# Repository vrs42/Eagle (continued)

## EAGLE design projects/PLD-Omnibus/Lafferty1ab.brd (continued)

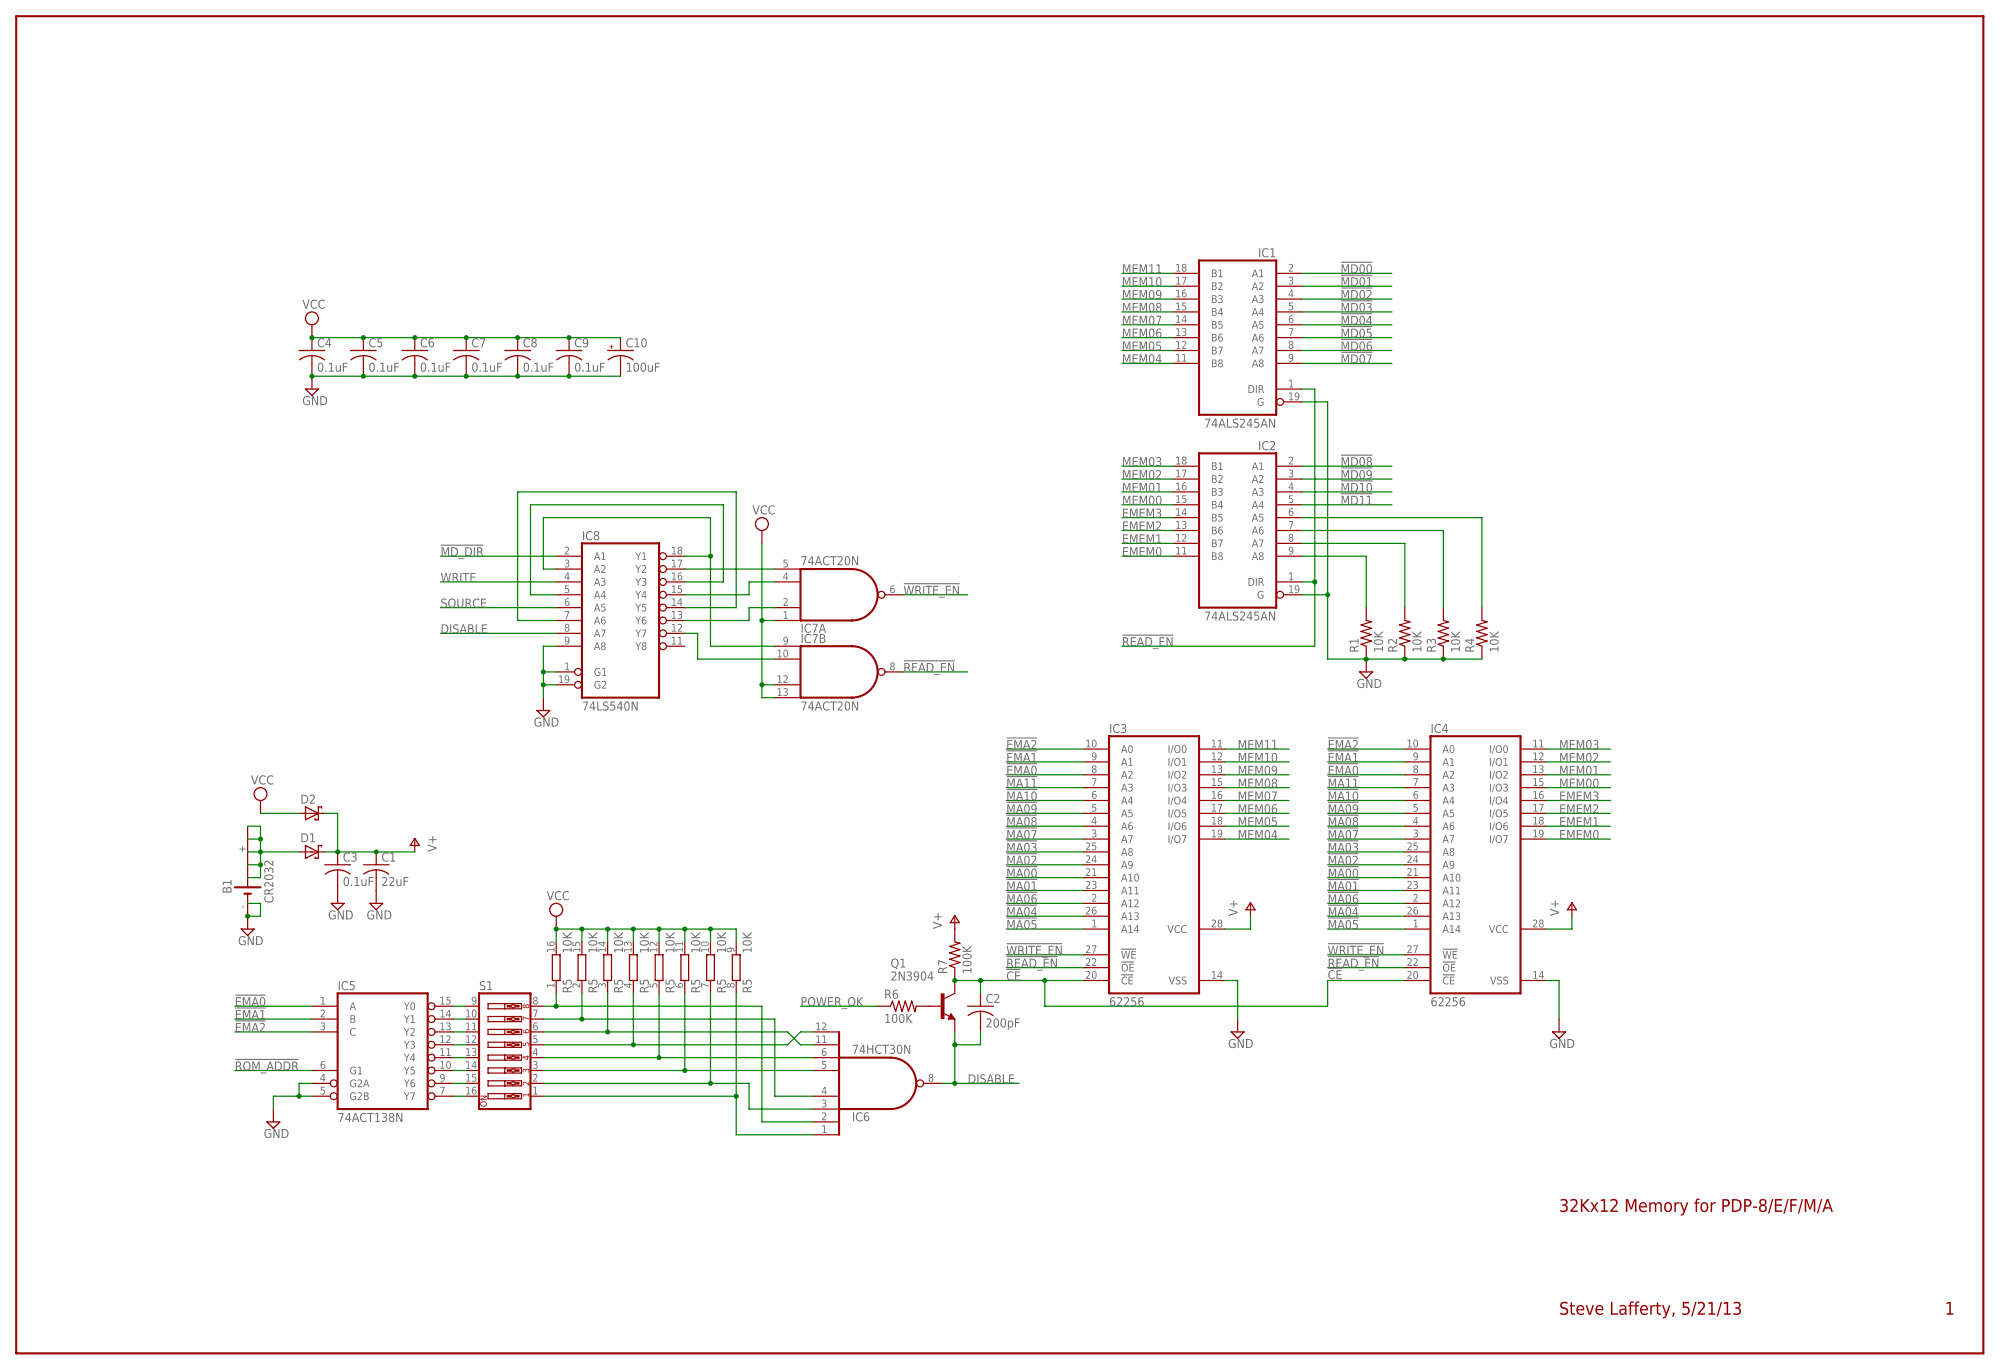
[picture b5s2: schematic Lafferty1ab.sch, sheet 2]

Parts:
B1: CR2032; B2430UNI
C1: 22uF; C050-025X075
C2: 200pF; C050-025X075
C3, C4, C5, C6, C7, C8, C9: 0.1uF; C050-025X075
C10: 100uF; E12-8
D1, D2: BAT19; DO35-10
IC1, IC2: 74ALS245AN; DIL20
IC3, IC4: 62256; DIL28-6
IC5: 74ACT138N; DIL16
IC6: 74HCT30N; DIL14
IC7: 74ACT20N; DIL14
IC8: 74LS540N; DIL20
Q1: 2N3904; TO92
R1, R2, R3, R4: 10K; 0207/10
R5: 10K; DIL16
R6, R7: 100K; 0207/10
S1: SW_DIP-8; EDG-08

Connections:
!CE: C2.1, IC3.20 (!CE), IC4.20 (!CE), Q1.1 (C), R7.1
!EMA0: IC3.8 (A2), IC4.8 (A2), IC5.1 (A); also elsewhere on the board
!EMA1: IC3.9 (A1), IC4.9 (A1), IC5.2 (B); also elsewhere on the board
!EMA2: IC3.10 (A0), IC4.10 (A0), IC5.3 (C); also elsewhere on the board
!MA00: IC3.21 (A10), IC4.21 (A10); also elsewhere on the board
!MA01: IC3.23 (A11), IC4.23 (A11); also elsewhere on the board
!MA02: IC3.24 (A9), IC4.24 (A9); also elsewhere on the board
!MA03: IC3.25 (A8), IC4.25 (A8); also elsewhere on the board
!MA04: IC3.26 (A13), IC4.26 (A13); also elsewhere on the board
!MA05: IC3.1 (A14), IC4.1 (A14); also elsewhere on the board
!MA06: IC3.2 (A12), IC4.2 (A12); also elsewhere on the board
!MA07: IC3.3 (A7), IC4.3 (A7); also elsewhere on the board
!MA08: IC3.4 (A6), IC4.4 (A6); also elsewhere on the board
!MA09: IC3.5 (A5), IC4.5 (A5); also elsewhere on the board
!MA10: IC3.6 (A4), IC4.6 (A4); also elsewhere on the board
!MA11: IC3.7 (A3), IC4.7 (A3); also elsewhere on the board
!MD00: IC1.2 (A1); also elsewhere on the board
!MD01: IC1.3 (A2); also elsewhere on the board
!MD02: IC1.4 (A3); also elsewhere on the board
!MD03: IC1.5 (A4); also elsewhere on the board
!MD04: IC1.6 (A5); also elsewhere on the board
!MD05: IC1.7 (A6); also elsewhere on the board
!MD06: IC1.8 (A7); also elsewhere on the board
!MD07: IC1.9 (A8); also elsewhere on the board
!MD08: IC2.2 (A1); also elsewhere on the board
!MD09: IC2.3 (A2); also elsewhere on the board
!MD10: IC2.4 (A3); also elsewhere on the board
!MD11: IC2.5 (A4); also elsewhere on the board
!MD_DIR: IC8.2 (A1); also elsewhere on the board
!READ_EN: IC1.1 (DIR), IC2.1 (DIR), IC3.22 (!OE), IC4.22 (!OE), IC7.8 (O)
!ROM_ADDR: IC5.6 (G1); also elsewhere on the board
!WRITE_EN: IC3.27 (!WE), IC4.27 (!WE), IC7.6 (O)
DISABLE: C2.2, IC6.8 (O), IC8.8 (A7), Q1.3 (E)
EMEM0: IC2.11 (B8), IC4.19 (I/O7)
EMEM1: IC2.12 (B7), IC4.18 (I/O6)
EMEM2: IC2.13 (B6), IC4.17 (I/O5)
EMEM3: IC2.14 (B5), IC4.16 (I/O4)
GND: B1.-, B1.-@1 (-), C1.2, C3.2, C4.2, C5.2, C6.2, C7.2, C8.2, C9.2, C10.-, IC1.10 (GND), IC1.19 (G), IC2.10 (GND), IC2.19 (G), IC3.14 (VSS), IC4.14 (VSS), IC5.4 (G2A), IC5.5 (G2B), IC5.8 (GND), IC6.7 (GND), IC7.7 (GND), IC8.1 (G1), IC8.9 (A8), IC8.10 (GND), IC8.19 (G2), R1.1, R2.1, R3.1, R4.1; also elsewhere on the board
MEM00: IC2.15 (B4), IC4.15 (I/O3)
MEM01: IC2.16 (B3), IC4.13 (I/O2)
MEM02: IC2.17 (B2), IC4.12 (I/O1)
MEM03: IC2.18 (B1), IC4.11 (I/O0)
MEM04: IC1.11 (B8), IC3.19 (I/O7)
MEM05: IC1.12 (B7), IC3.18 (I/O6)
MEM06: IC1.13 (B6), IC3.17 (I/O5)
MEM07: IC1.14 (B5), IC3.16 (I/O4)
MEM08: IC1.15 (B4), IC3.15 (I/O3)
MEM09: IC1.16 (B3), IC3.13 (I/O2)
MEM10: IC1.17 (B2), IC3.12 (I/O1)
MEM11: IC1.18 (B1), IC3.11 (I/O0)
unnamed: IC5.7 (Y7), S1.16
unnamed: IC5.9 (Y6), S1.15
unnamed: IC5.10 (Y5), S1.14
unnamed: IC5.11 (Y4), S1.13
unnamed: IC5.12 (Y3), S1.12
unnamed: IC5.13 (Y2), S1.11
unnamed: IC5.14 (Y1), S1.10
unnamed: IC5.15 (Y0), S1.9
unnamed: B1.+, B1.+@1 (+), B1.+@2 (+), B1.+@3 (+), B1.+@4 (+), D1.A
unnamed: IC6.12 (I7), R5.4 (1), S1.5
unnamed: IC6.11 (I6), R5.3 (1), S1.6
unnamed: IC6.6 (I5), R5.5 (1), S1.4
unnamed: IC6.5 (I4), R5.6 (1), S1.3
unnamed: IC6.3 (I2), R5.7 (1), S1.2
unnamed: IC6.1 (I0), R5.8 (1), S1.1
unnamed: IC6.2 (I1), R5.1, S1.8
unnamed: IC6.4 (I3), R5.2 (1), S1.7
unnamed: IC7.5 (I3), IC8.17 (Y2)
unnamed: IC2.6 (A5), R4.2
unnamed: Q1.2 (B), R6.2
unnamed: IC2.7 (A6), R3.2
unnamed: IC2.8 (A7), R2.2
unnamed: IC2.9 (A8), R1.2
unnamed: IC8.5 (A4), IC8.16 (Y3)
unnamed: IC7.9 (I0), IC8.3 (A2), IC8.18 (Y1)
unnamed: IC8.7 (A6), IC8.14 (Y5)
unnamed: IC7.2 (I1), IC8.13 (Y6)
unnamed: IC7.4 (I2), IC8.15 (Y4)
unnamed: IC7.10 (I1), IC8.12 (Y7)
POWER_OK: R6.1; also elsewhere on the board
SOURCE: IC8.6 (A5); also elsewhere on the board
V+: C1.1, C3.1, D1.C, D2.C, IC3.28 (VCC), IC4.28 (VCC), R7.2
VCC: C4.1, C5.1, C6.1, C7.1, C8.1, C9.1, C10.+, D2.A, IC1.20 (VCC), IC2.20 (VCC), IC5.16 (VCC), IC6.14 (VCC), IC7.1 (I0), IC7.12 (I2), IC7.13 (I3), IC7.14 (VCC), IC8.20 (VCC), R5.9 (2), R5.10 (2), R5.11 (2), R5.12 (2), R5.13 (2), R5.14 (2), R5.15 (2), R5.16 (2); also elsewhere on the board
WRITE: IC8.4 (A3); also elsewhere on the board

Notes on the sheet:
32Kx12 Memory for PDP-8/E/F/M/A
Steve Lafferty, 5/21/13

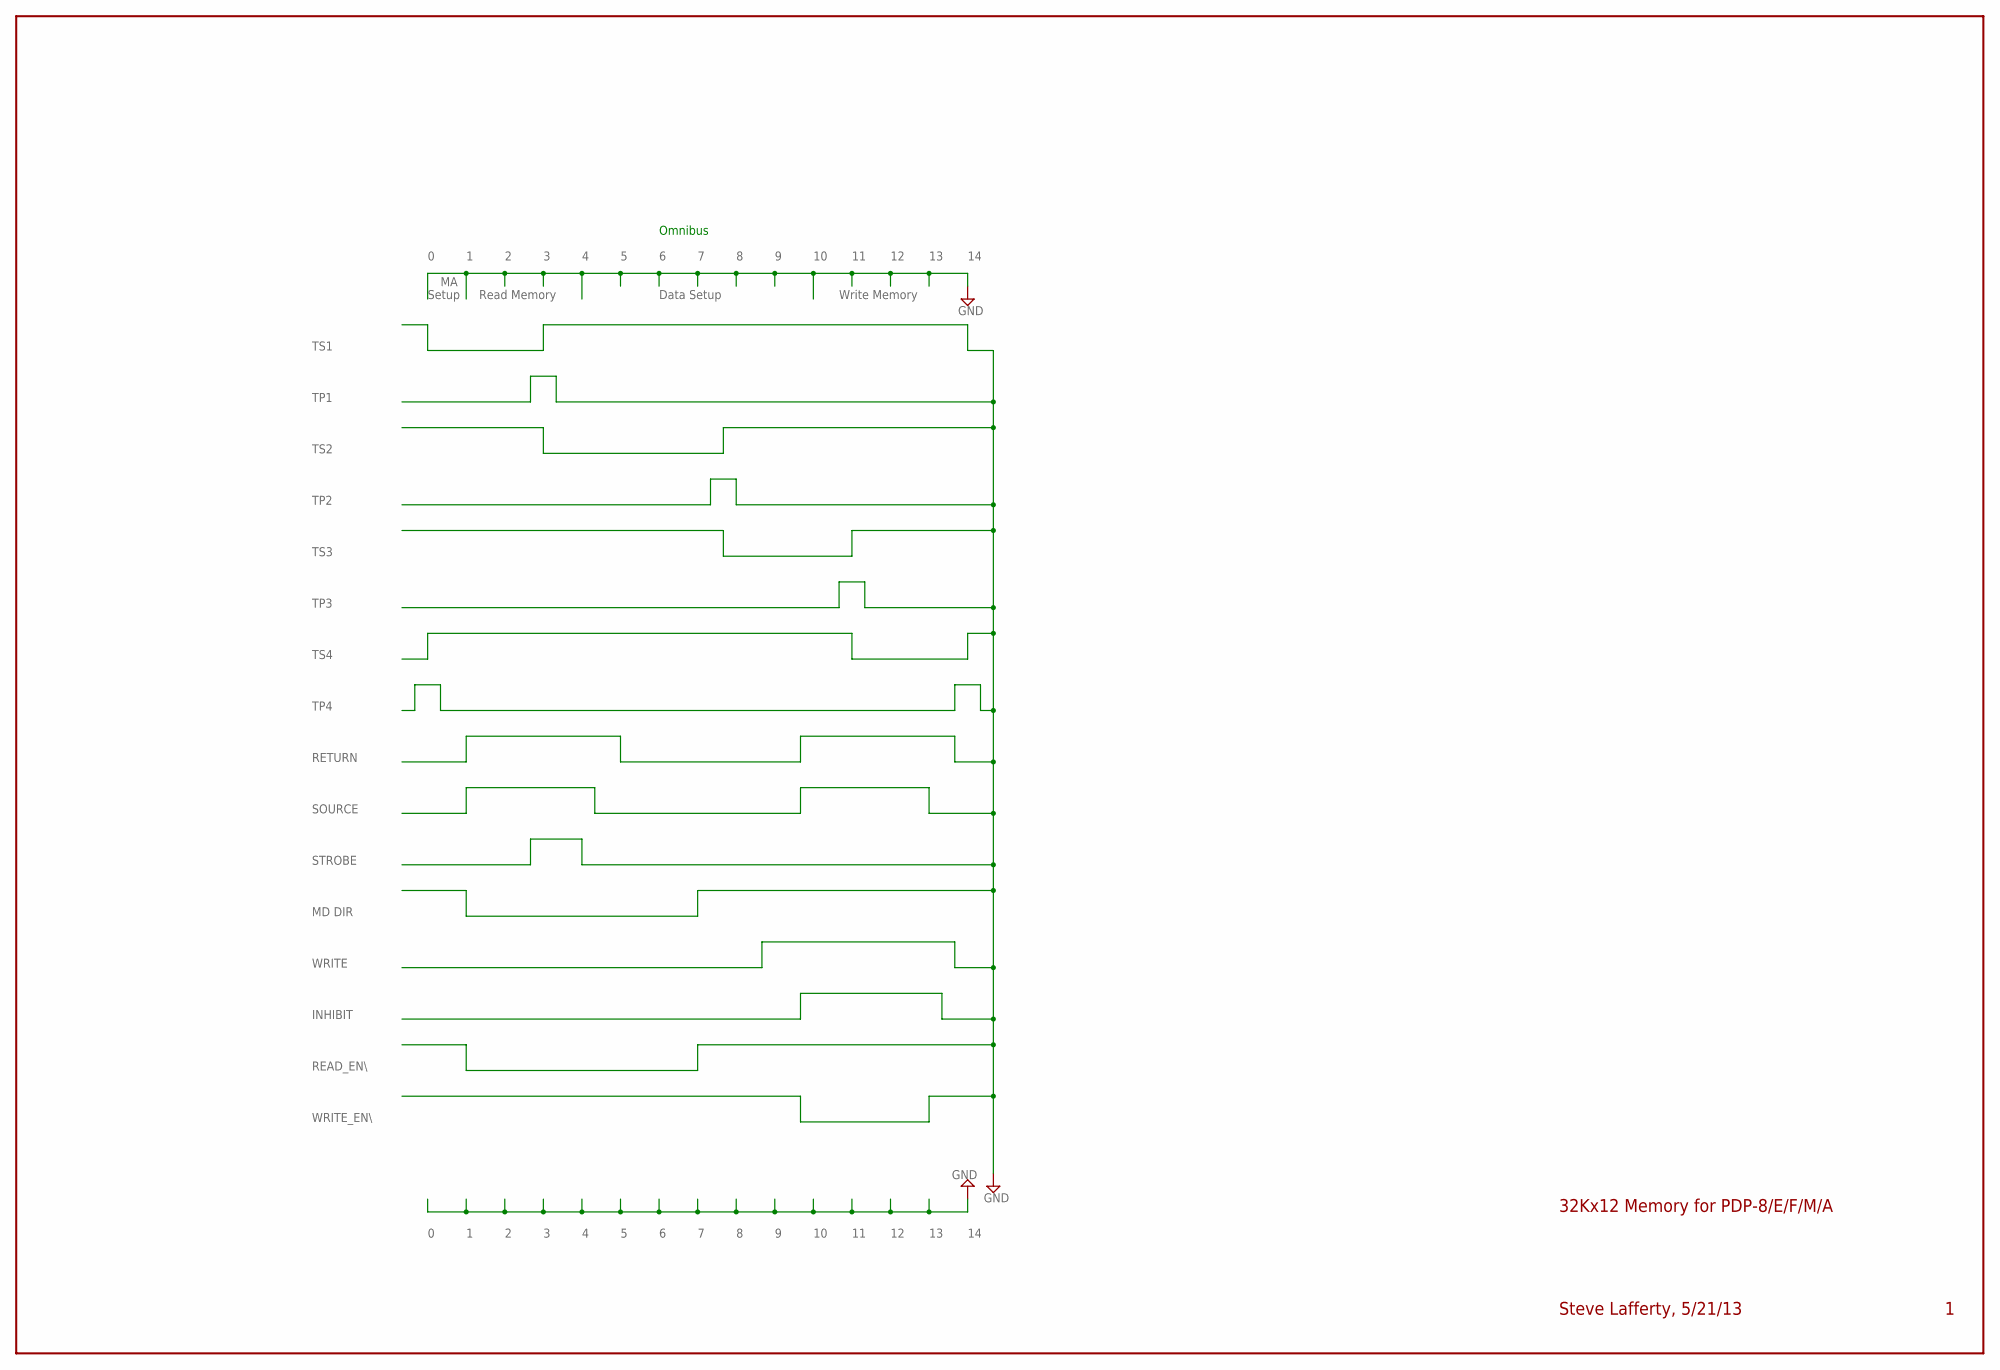
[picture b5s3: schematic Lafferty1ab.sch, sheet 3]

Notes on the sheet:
TS1
TS2
TS3
TS4
TP1
TP2
TP3
TP4
INHIBIT
WRITE
STROBE
SOURCE
RETURN
MD DIR
Setup
Read Memory
Data Setup
Write Memory
Omnibus
READ_EN\\
WRITE_EN\\
32Kx12 Memory for PDP-8/E/F/M/A
Steve Lafferty, 5/21/13

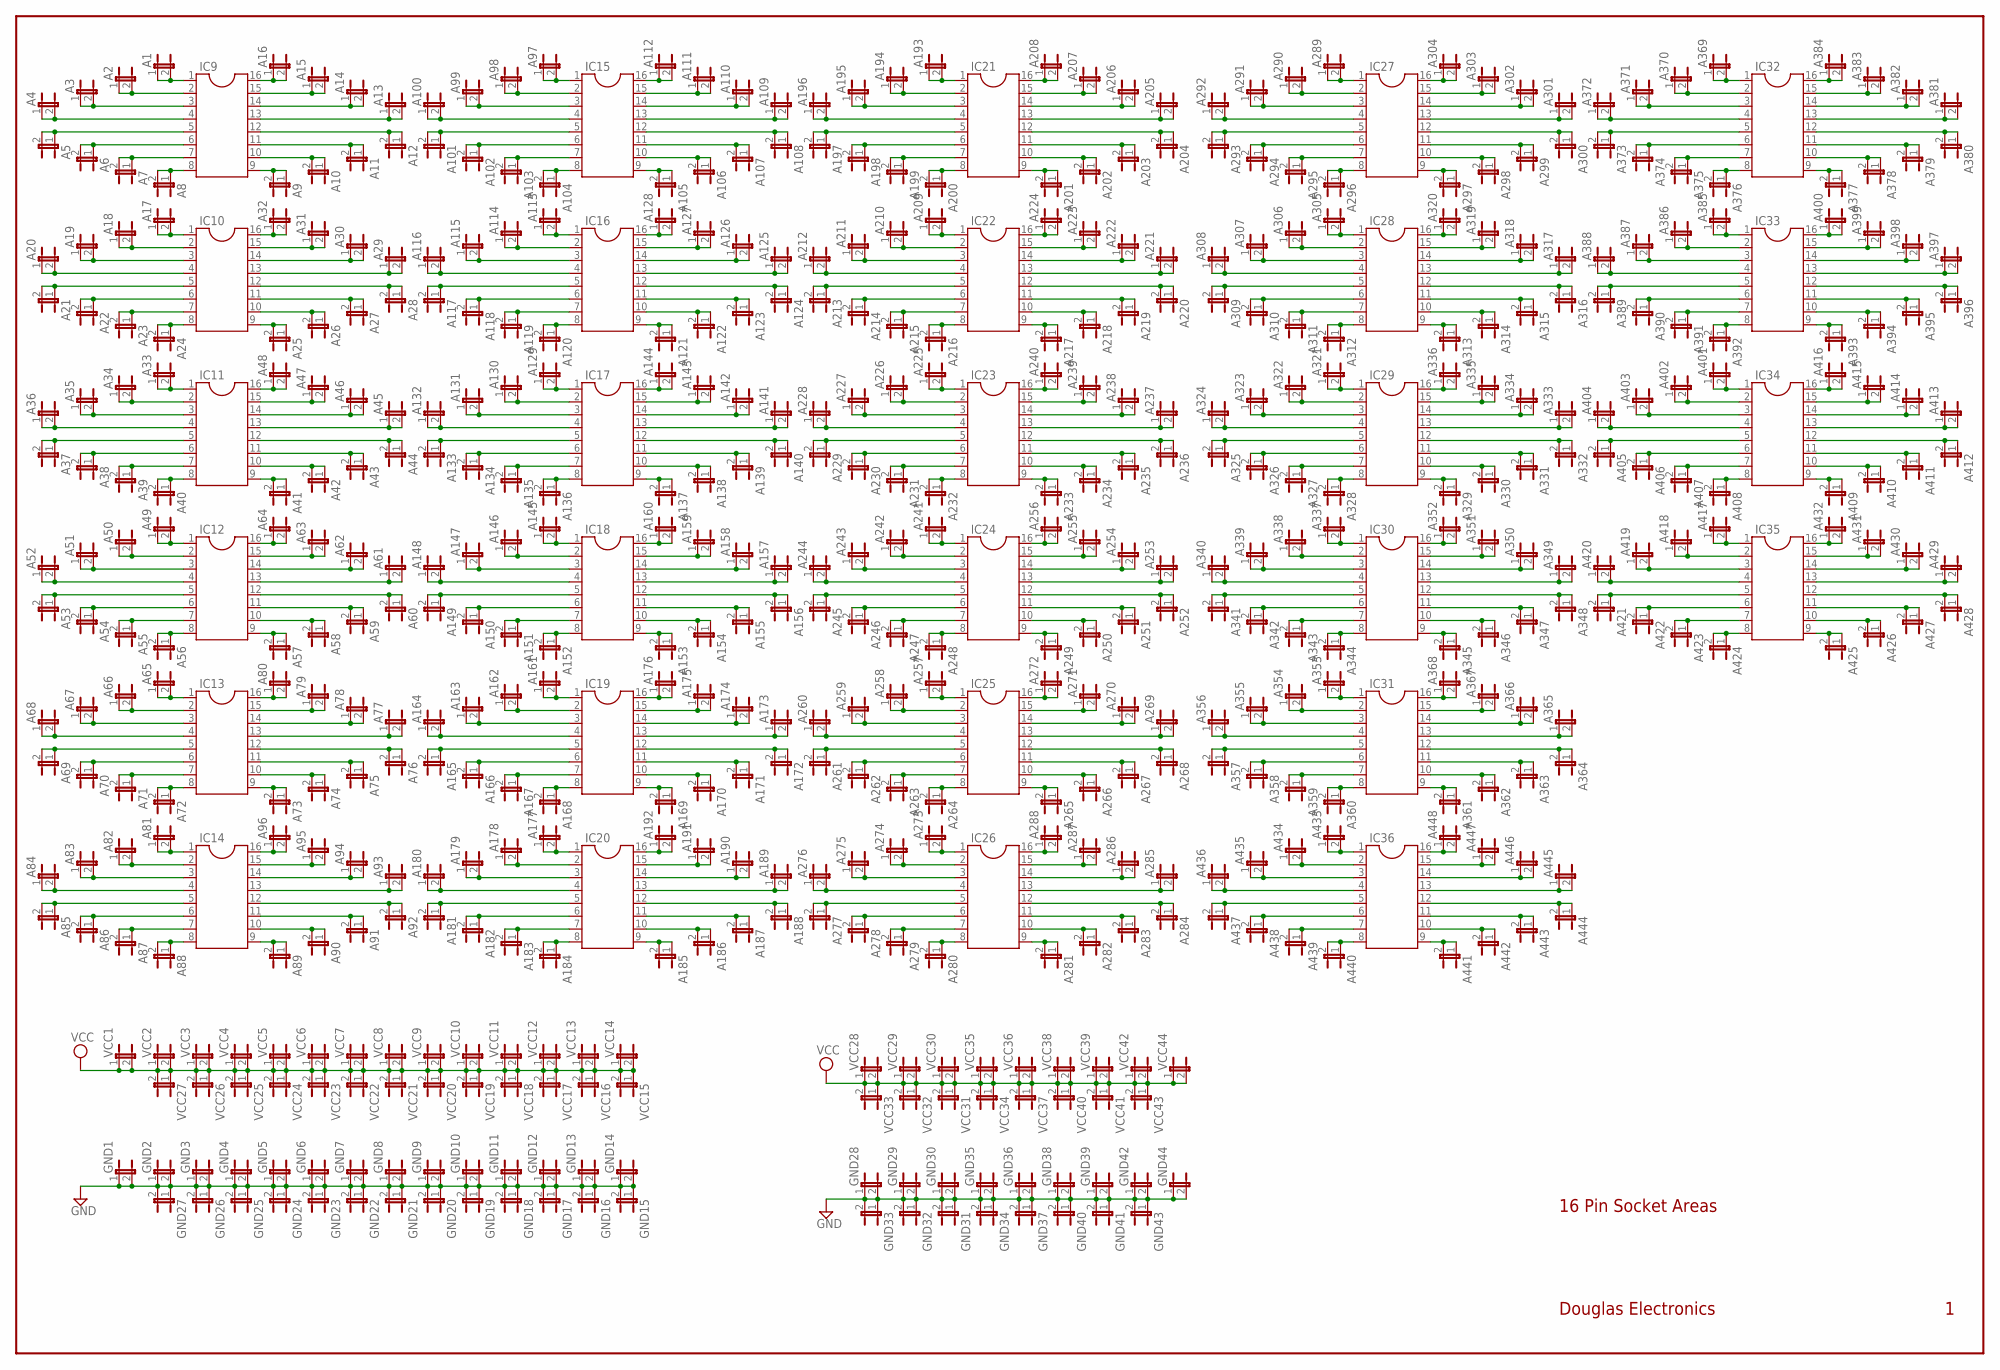
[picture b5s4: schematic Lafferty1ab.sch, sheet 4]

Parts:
A1, A2, A3, A4, A5, A6, A7, A8, A9, A10, A11, A12, A13, A14, A15, A16, A17, A18, A19, A20, A21, A22, A23, A24, A25, A26, A27, A28, A29, A30, A31, A32, A33, A34, A35, A36, A37, A38, A39, A40, A41, A42, A43, A44, A45, A46, A47, A48, A49, A50, A51, A52, A53, A54, A55, A56, A57, A58, A59, A60, A61, A62, A63, A64, A65, A66, A67, A68, A69, A70, A71, A72, A73, A74, A75, A76, A77, A78, A79, A80, A81, A82, A83, A84, A85, A86, A87, A88, A89, A90, A91, A92, A93, A94, A95, A96, A97, A98, A99, A100, A101, A102, A103, A104, A105, A106, A107, A108, A109, A110, A111, A112, A113, A114, A115, A116, A117, A118, A119, A120, A121, A122, A123, A124, A125, A126, A127, A128, A129, A130, A131, A132, A133, A134, A135, A136, A137, A138, A139, A140, A141, A142, A143, A144, A145, A146, A147, A148, A149, A150, A151, A152, A153, A154, A155, A156, A157, A158, A159, A160, A161, A162, A163, A164, A165, A166, A167, A168, A169, A170, A171, A172, A173, A174, A175, A176, A177, A178, A179, A180, A181, A182, A183, A184, A185, A186, A187, A188, A189, A190, A191, A192, A193, A194, A195, A196, A197, A198, A199, A200, A201, A202, A203, A204, A205, A206, A207, A208, A209, A210, A211, A212, A213, A214, A215, A216, A217, A218, A219, A220, A221, A222, A223, A224, A225, A226, A227, A228, A229, A230, A231, A232, A233, A234, A235, A236, A237, A238, A239, A240, A241, A242, A243, A244, A245, A246, A247, A248, A249, A250, A251, A252, A253, A254, A255, A256, A257, A258, A259, A260, A261, A262, A263, A264, A265, A266, A267, A268, A269, A270, A271, A272, A273, A274, A275, A276, A277, A278, A279, A280, A281, A282, A283, A284, A285, A286, A287, A288, A289, A290, A291, A292, A293, A294, A295, A296, A297, A298, A299, A300, A301, A302, A303, A304, A305, A306, A307, A308, A309, A310, A311, A312, A313, A314, A315, A316, A317, A318, A319, A320, A321, A322, A323, A324, A325, A326, A327, A328, A329, A330, A331, A332, A333, A334, A335, A336, A337, A338, A339, A340, A341, A342, A343, A344, A345, A346, A347, A348, A349, A350, A351, A352, A353, A354, A355, A356, A357, A358, A359, A360, A361, A362, A363, A364, A365, A366, A367, A368, A369, A370, A371, A372, A373, A374, A375, A376, A377, A378, A379, A380, A381, A382, A383, A384, A385, A386, A387, A388, A389, A390, A391, A392, A393, A394, A395, A396, A397, A398, A399, A400, A401, A402, A403, A404, A405, A406, A407, A408, A409, A410, A411, A412, A413, A414, A415, A416, A417, A418, A419, A420, A421, A422, A423, A424, A425, A426, A427, A428, A429, A430, A431, A432, A433, A434, A435, A436, A437, A438, A439, A440, A441, A442, A443, A444, A445, A446, A447, A448: JP1E; JP1
GND1, GND2, GND3, GND4, GND5, GND6, GND7, GND8, GND9, GND10, GND11, GND12, GND13, GND14, GND15, GND16, GND17, GND18, GND19, GND20, GND21, GND22, GND23, GND24, GND25, GND26, GND27, GND28, GND29, GND30, GND31, GND32, GND33, GND34, GND35, GND36, GND37, GND38, GND39, GND40, GND41, GND42, GND43, GND44: JP1E; JP1
IC9, IC10, IC11, IC12, IC13, IC14, IC15, IC16, IC17, IC18, IC19, IC20, IC21, IC22, IC23, IC24, IC25, IC26, IC27, IC28, IC29, IC30, IC31, IC32, IC33, IC34, IC35, IC36: DIL16
VCC1, VCC2, VCC3, VCC4, VCC5, VCC6, VCC7, VCC8, VCC9, VCC10, VCC11, VCC12, VCC13, VCC14, VCC15, VCC16, VCC17, VCC18, VCC19, VCC20, VCC21, VCC22, VCC23, VCC24, VCC25, VCC26, VCC27, VCC28, VCC29, VCC30, VCC31, VCC32, VCC33, VCC34, VCC35, VCC36, VCC37, VCC38, VCC39, VCC40, VCC41, VCC42, VCC43, VCC44: JP1E; JP1

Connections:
GND: GND1.1, GND1.2, GND2.1, GND2.2, GND3.1, GND3.2, GND4.1, GND4.2, GND5.1, GND5.2, GND6.1, GND6.2, GND7.1, GND7.2, GND8.1, GND8.2, GND9.1, GND9.2, GND10.1, GND10.2, GND11.1, GND11.2, GND12.1, GND12.2, GND13.1, GND13.2, GND14.1, GND14.2, GND15.1, GND15.2, GND16.1, GND16.2, GND17.1, GND17.2, GND18.1, GND18.2, GND19.1, GND19.2, GND20.1, GND20.2, GND21.1, GND21.2, GND22.1, GND22.2, GND23.1, GND23.2, GND24.1, GND24.2, GND25.1, GND25.2, GND26.1, GND26.2, GND27.1, GND27.2, GND28.1, GND28.2, GND29.1, GND29.2, GND30.1, GND30.2, GND31.1, GND31.2, GND32.1, GND32.2, GND33.1, GND33.2, GND34.1, GND34.2, GND35.1, GND35.2, GND36.1, GND36.2, GND37.1, GND37.2, GND38.1, GND38.2, GND39.1, GND39.2, GND40.1, GND40.2, GND41.1, GND41.2, GND42.1, GND42.2, GND43.1, GND43.2, GND44.1, GND44.2; also elsewhere on the board
unnamed: A16.1, A16.2, IC9.16
unnamed: A14.1, A14.2, IC9.14
unnamed: A9.1, A9.2, IC9.9
unnamed: A15.1, A15.2, IC9.15
unnamed: A10.1, A10.2, IC9.10
unnamed: A13.1, A13.2, IC9.13
unnamed: A32.1, A32.2, IC10.16
unnamed: A12.1, A12.2, IC9.12
unnamed: A11.1, A11.2, IC9.11
unnamed: A1.1, A1.2, IC9.1
unnamed: A8.1, A8.2, IC9.8
unnamed: A2.1, A2.2, IC9.2
unnamed: A7.1, A7.2, IC9.7
unnamed: A3.1, A3.2, IC9.3
unnamed: A4.1, A4.2, IC9.4
unnamed: A5.1, A5.2, IC9.5
unnamed: A6.1, A6.2, IC9.6
unnamed: A25.1, A25.2, IC10.9
unnamed: A31.1, A31.2, IC10.15
unnamed: A26.1, A26.2, IC10.10
unnamed: A30.1, A30.2, IC10.14
unnamed: A29.1, A29.2, IC10.13
unnamed: A28.1, A28.2, IC10.12
unnamed: A27.1, A27.2, IC10.11
unnamed: A17.1, A17.2, IC10.1
unnamed: A24.1, A24.2, IC10.8
unnamed: A18.1, A18.2, IC10.2
unnamed: A23.1, A23.2, IC10.7
unnamed: A19.1, A19.2, IC10.3
unnamed: A20.1, A20.2, IC10.4
unnamed: A21.1, A21.2, IC10.5
unnamed: A22.1, A22.2, IC10.6
unnamed: A48.1, A48.2, IC11.16
unnamed: A41.1, A41.2, IC11.9
unnamed: A47.1, A47.2, IC11.15
unnamed: A42.1, A42.2, IC11.10
unnamed: A46.1, A46.2, IC11.14
unnamed: A45.1, A45.2, IC11.13
unnamed: A44.1, A44.2, IC11.12
unnamed: A43.1, A43.2, IC11.11
unnamed: A33.1, A33.2, IC11.1
unnamed: A40.1, A40.2, IC11.8
unnamed: A34.1, A34.2, IC11.2
unnamed: A39.1, A39.2, IC11.7
unnamed: A35.1, A35.2, IC11.3
unnamed: A36.1, A36.2, IC11.4
unnamed: A37.1, A37.2, IC11.5
unnamed: A38.1, A38.2, IC11.6
unnamed: A64.1, A64.2, IC12.16
unnamed: A57.1, A57.2, IC12.9
unnamed: A63.1, A63.2, IC12.15
unnamed: A58.1, A58.2, IC12.10
unnamed: A62.1, A62.2, IC12.14
unnamed: A61.1, A61.2, IC12.13
unnamed: A60.1, A60.2, IC12.12
unnamed: A59.1, A59.2, IC12.11
unnamed: A49.1, A49.2, IC12.1
unnamed: A56.1, A56.2, IC12.8
unnamed: A50.1, A50.2, IC12.2
unnamed: A55.1, A55.2, IC12.7
unnamed: A51.1, A51.2, IC12.3
unnamed: A52.1, A52.2, IC12.4
unnamed: A53.1, A53.2, IC12.5
unnamed: A54.1, A54.2, IC12.6
unnamed: A80.1, A80.2, IC13.16
unnamed: A73.1, A73.2, IC13.9
unnamed: A79.1, A79.2, IC13.15
unnamed: A74.1, A74.2, IC13.10
unnamed: A78.1, A78.2, IC13.14
unnamed: A77.1, A77.2, IC13.13
unnamed: A76.1, A76.2, IC13.12
unnamed: A75.1, A75.2, IC13.11
unnamed: A65.1, A65.2, IC13.1
unnamed: A72.1, A72.2, IC13.8
unnamed: A66.1, A66.2, IC13.2
unnamed: A71.1, A71.2, IC13.7
unnamed: A67.1, A67.2, IC13.3
unnamed: A68.1, A68.2, IC13.4
unnamed: A69.1, A69.2, IC13.5
unnamed: A70.1, A70.2, IC13.6
unnamed: A96.1, A96.2, IC14.16
unnamed: A89.1, A89.2, IC14.9
unnamed: A95.1, A95.2, IC14.15
unnamed: A90.1, A90.2, IC14.10
unnamed: A94.1, A94.2, IC14.14
unnamed: A93.1, A93.2, IC14.13
unnamed: A92.1, A92.2, IC14.12
unnamed: A91.1, A91.2, IC14.11
unnamed: A81.1, A81.2, IC14.1
unnamed: A88.1, A88.2, IC14.8
unnamed: A82.1, A82.2, IC14.2
unnamed: A87.1, A87.2, IC14.7
unnamed: A83.1, A83.2, IC14.3
unnamed: A84.1, A84.2, IC14.4
unnamed: A85.1, A85.2, IC14.5
unnamed: A86.1, A86.2, IC14.6
unnamed: A112.1, A112.2, IC15.16
unnamed: A105.1, A105.2, IC15.9
unnamed: A111.1, A111.2, IC15.15
unnamed: A106.1, A106.2, IC15.10
unnamed: A110.1, A110.2, IC15.14
unnamed: A109.1, A109.2, IC15.13
unnamed: A108.1, A108.2, IC15.12
unnamed: A107.1, A107.2, IC15.11
unnamed: A97.1, A97.2, IC15.1
unnamed: A104.1, A104.2, IC15.8
unnamed: A98.1, A98.2, IC15.2
unnamed: A103.1, A103.2, IC15.7
unnamed: A99.1, A99.2, IC15.3
unnamed: A100.1, A100.2, IC15.4
unnamed: A101.1, A101.2, IC15.5
unnamed: A102.1, A102.2, IC15.6
unnamed: A128.1, A128.2, IC16.16
unnamed: A121.1, A121.2, IC16.9
unnamed: A127.1, A127.2, IC16.15
unnamed: A122.1, A122.2, IC16.10
unnamed: A126.1, A126.2, IC16.14
unnamed: A125.1, A125.2, IC16.13
unnamed: A124.1, A124.2, IC16.12
unnamed: A123.1, A123.2, IC16.11
unnamed: A113.1, A113.2, IC16.1
unnamed: A120.1, A120.2, IC16.8
unnamed: A114.1, A114.2, IC16.2
unnamed: A119.1, A119.2, IC16.7
unnamed: A115.1, A115.2, IC16.3
unnamed: A116.1, A116.2, IC16.4
unnamed: A117.1, A117.2, IC16.5
unnamed: A118.1, A118.2, IC16.6
unnamed: A144.1, A144.2, IC17.16
unnamed: A137.1, A137.2, IC17.9
unnamed: A143.1, A143.2, IC17.15
unnamed: A138.1, A138.2, IC17.10
unnamed: A142.1, A142.2, IC17.14
unnamed: A141.1, A141.2, IC17.13
unnamed: A140.1, A140.2, IC17.12
unnamed: A139.1, A139.2, IC17.11
unnamed: A129.1, A129.2, IC17.1
unnamed: A136.1, A136.2, IC17.8
unnamed: A130.1, A130.2, IC17.2
unnamed: A135.1, A135.2, IC17.7
unnamed: A131.1, A131.2, IC17.3
unnamed: A132.1, A132.2, IC17.4
unnamed: A133.1, A133.2, IC17.5
unnamed: A134.1, A134.2, IC17.6
unnamed: A160.1, A160.2, IC18.16
unnamed: A153.1, A153.2, IC18.9
unnamed: A159.1, A159.2, IC18.15
unnamed: A154.1, A154.2, IC18.10
unnamed: A158.1, A158.2, IC18.14
unnamed: A157.1, A157.2, IC18.13
unnamed: A156.1, A156.2, IC18.12
unnamed: A155.1, A155.2, IC18.11
unnamed: A145.1, A145.2, IC18.1
unnamed: A152.1, A152.2, IC18.8
unnamed: A146.1, A146.2, IC18.2
unnamed: A151.1, A151.2, IC18.7
unnamed: A147.1, A147.2, IC18.3
unnamed: A148.1, A148.2, IC18.4
unnamed: A149.1, A149.2, IC18.5
unnamed: A150.1, A150.2, IC18.6
unnamed: A176.1, A176.2, IC19.16
unnamed: A169.1, A169.2, IC19.9
unnamed: A175.1, A175.2, IC19.15
unnamed: A170.1, A170.2, IC19.10
unnamed: A174.1, A174.2, IC19.14
unnamed: A173.1, A173.2, IC19.13
unnamed: A172.1, A172.2, IC19.12
unnamed: A171.1, A171.2, IC19.11
unnamed: A161.1, A161.2, IC19.1
unnamed: A168.1, A168.2, IC19.8
unnamed: A162.1, A162.2, IC19.2
unnamed: A167.1, A167.2, IC19.7
unnamed: A163.1, A163.2, IC19.3
unnamed: A164.1, A164.2, IC19.4
unnamed: A165.1, A165.2, IC19.5
unnamed: A166.1, A166.2, IC19.6
unnamed: A192.1, A192.2, IC20.16
unnamed: A185.1, A185.2, IC20.9
unnamed: A191.1, A191.2, IC20.15
unnamed: A186.1, A186.2, IC20.10
unnamed: A190.1, A190.2, IC20.14
unnamed: A189.1, A189.2, IC20.13
unnamed: A188.1, A188.2, IC20.12
unnamed: A187.1, A187.2, IC20.11
unnamed: A177.1, A177.2, IC20.1
unnamed: A184.1, A184.2, IC20.8
unnamed: A178.1, A178.2, IC20.2
unnamed: A183.1, A183.2, IC20.7
unnamed: A179.1, A179.2, IC20.3
unnamed: A180.1, A180.2, IC20.4
unnamed: A181.1, A181.2, IC20.5
unnamed: A182.1, A182.2, IC20.6
unnamed: A304.1, A304.2, IC27.16
unnamed: A297.1, A297.2, IC27.9
unnamed: A208.1, A208.2, IC21.16
unnamed: A201.1, A201.2, IC21.9
unnamed: A207.1, A207.2, IC21.15
unnamed: A202.1, A202.2, IC21.10
unnamed: A206.1, A206.2, IC21.14
unnamed: A205.1, A205.2, IC21.13
unnamed: A204.1, A204.2, IC21.12
unnamed: A203.1, A203.2, IC21.11
unnamed: A193.1, A193.2, IC21.1
unnamed: A200.1, A200.2, IC21.8
unnamed: A194.1, A194.2, IC21.2
unnamed: A199.1, A199.2, IC21.7
unnamed: A195.1, A195.2, IC21.3
unnamed: A196.1, A196.2, IC21.4
unnamed: A197.1, A197.2, IC21.5
unnamed: A198.1, A198.2, IC21.6
unnamed: A224.1, A224.2, IC22.16
unnamed: A217.1, A217.2, IC22.9
unnamed: A223.1, A223.2, IC22.15
unnamed: A218.1, A218.2, IC22.10
unnamed: A222.1, A222.2, IC22.14
unnamed: A221.1, A221.2, IC22.13
unnamed: A220.1, A220.2, IC22.12
unnamed: A219.1, A219.2, IC22.11
unnamed: A209.1, A209.2, IC22.1
unnamed: A216.1, A216.2, IC22.8
unnamed: A210.1, A210.2, IC22.2
unnamed: A215.1, A215.2, IC22.7
unnamed: A211.1, A211.2, IC22.3
unnamed: A212.1, A212.2, IC22.4
unnamed: A213.1, A213.2, IC22.5
unnamed: A214.1, A214.2, IC22.6
unnamed: A240.1, A240.2, IC23.16
unnamed: A233.1, A233.2, IC23.9
unnamed: A239.1, A239.2, IC23.15
unnamed: A234.1, A234.2, IC23.10
unnamed: A238.1, A238.2, IC23.14
unnamed: A237.1, A237.2, IC23.13
unnamed: A236.1, A236.2, IC23.12
unnamed: A235.1, A235.2, IC23.11
unnamed: A225.1, A225.2, IC23.1
unnamed: A232.1, A232.2, IC23.8
unnamed: A226.1, A226.2, IC23.2
unnamed: A231.1, A231.2, IC23.7
unnamed: A227.1, A227.2, IC23.3
unnamed: A228.1, A228.2, IC23.4
unnamed: A229.1, A229.2, IC23.5
unnamed: A230.1, A230.2, IC23.6
unnamed: A256.1, A256.2, IC24.16
unnamed: A249.1, A249.2, IC24.9
unnamed: A255.1, A255.2, IC24.15
unnamed: A250.1, A250.2, IC24.10
unnamed: A254.1, A254.2, IC24.14
unnamed: A253.1, A253.2, IC24.13
unnamed: A252.1, A252.2, IC24.12
unnamed: A251.1, A251.2, IC24.11
unnamed: A241.1, A241.2, IC24.1
unnamed: A248.1, A248.2, IC24.8
unnamed: A242.1, A242.2, IC24.2
unnamed: A247.1, A247.2, IC24.7
unnamed: A243.1, A243.2, IC24.3
unnamed: A244.1, A244.2, IC24.4
unnamed: A245.1, A245.2, IC24.5
unnamed: A246.1, A246.2, IC24.6
unnamed: A272.1, A272.2, IC25.16
unnamed: A265.1, A265.2, IC25.9
unnamed: A271.1, A271.2, IC25.15
unnamed: A266.1, A266.2, IC25.10
unnamed: A270.1, A270.2, IC25.14
unnamed: A269.1, A269.2, IC25.13
unnamed: A268.1, A268.2, IC25.12
unnamed: A267.1, A267.2, IC25.11
unnamed: A257.1, A257.2, IC25.1
unnamed: A264.1, A264.2, IC25.8
unnamed: A258.1, A258.2, IC25.2
unnamed: A263.1, A263.2, IC25.7
unnamed: A259.1, A259.2, IC25.3
unnamed: A260.1, A260.2, IC25.4
unnamed: A261.1, A261.2, IC25.5
unnamed: A262.1, A262.2, IC25.6
unnamed: A288.1, A288.2, IC26.16
unnamed: A281.1, A281.2, IC26.9
unnamed: A287.1, A287.2, IC26.15
unnamed: A282.1, A282.2, IC26.10
unnamed: A286.1, A286.2, IC26.14
unnamed: A285.1, A285.2, IC26.13
unnamed: A284.1, A284.2, IC26.12
unnamed: A283.1, A283.2, IC26.11
unnamed: A273.1, A273.2, IC26.1
unnamed: A280.1, A280.2, IC26.8
unnamed: A274.1, A274.2, IC26.2
unnamed: A279.1, A279.2, IC26.7
unnamed: A275.1, A275.2, IC26.3
unnamed: A276.1, A276.2, IC26.4
unnamed: A277.1, A277.2, IC26.5
unnamed: A278.1, A278.2, IC26.6
unnamed: A303.1, A303.2, IC27.15
unnamed: A298.1, A298.2, IC27.10
unnamed: A302.1, A302.2, IC27.14
unnamed: A301.1, A301.2, IC27.13
unnamed: A300.1, A300.2, IC27.12
unnamed: A299.1, A299.2, IC27.11
unnamed: A289.1, A289.2, IC27.1
unnamed: A296.1, A296.2, IC27.8
unnamed: A290.1, A290.2, IC27.2
unnamed: A295.1, A295.2, IC27.7
unnamed: A291.1, A291.2, IC27.3
unnamed: A292.1, A292.2, IC27.4
unnamed: A293.1, A293.2, IC27.5
unnamed: A294.1, A294.2, IC27.6
unnamed: A320.1, A320.2, IC28.16
unnamed: A313.1, A313.2, IC28.9
unnamed: A319.1, A319.2, IC28.15
unnamed: A314.1, A314.2, IC28.10
unnamed: A318.1, A318.2, IC28.14
unnamed: A317.1, A317.2, IC28.13
unnamed: A316.1, A316.2, IC28.12
unnamed: A315.1, A315.2, IC28.11
unnamed: A305.1, A305.2, IC28.1
unnamed: A312.1, A312.2, IC28.8
unnamed: A306.1, A306.2, IC28.2
unnamed: A311.1, A311.2, IC28.7
unnamed: A307.1, A307.2, IC28.3
unnamed: A308.1, A308.2, IC28.4
unnamed: A309.1, A309.2, IC28.5
unnamed: A310.1, A310.2, IC28.6
unnamed: A336.1, A336.2, IC29.16
unnamed: A329.1, A329.2, IC29.9
unnamed: A335.1, A335.2, IC29.15
unnamed: A330.1, A330.2, IC29.10
unnamed: A334.1, A334.2, IC29.14
unnamed: A333.1, A333.2, IC29.13
unnamed: A332.1, A332.2, IC29.12
unnamed: A331.1, A331.2, IC29.11
unnamed: A321.1, A321.2, IC29.1
unnamed: A328.1, A328.2, IC29.8
unnamed: A322.1, A322.2, IC29.2
unnamed: A327.1, A327.2, IC29.7
unnamed: A323.1, A323.2, IC29.3
unnamed: A324.1, A324.2, IC29.4
unnamed: A325.1, A325.2, IC29.5
unnamed: A326.1, A326.2, IC29.6
unnamed: A352.1, A352.2, IC30.16
unnamed: A345.1, A345.2, IC30.9
unnamed: A351.1, A351.2, IC30.15
unnamed: A346.1, A346.2, IC30.10
unnamed: A350.1, A350.2, IC30.14
unnamed: A349.1, A349.2, IC30.13
unnamed: A348.1, A348.2, IC30.12
unnamed: A347.1, A347.2, IC30.11
unnamed: A337.1, A337.2, IC30.1
unnamed: A344.1, A344.2, IC30.8
unnamed: A338.1, A338.2, IC30.2
unnamed: A343.1, A343.2, IC30.7
unnamed: A339.1, A339.2, IC30.3
unnamed: A340.1, A340.2, IC30.4
unnamed: A341.1, A341.2, IC30.5
unnamed: A342.1, A342.2, IC30.6
unnamed: A368.1, A368.2, IC31.16
unnamed: A361.1, A361.2, IC31.9
unnamed: A367.1, A367.2, IC31.15
unnamed: A362.1, A362.2, IC31.10
unnamed: A366.1, A366.2, IC31.14
unnamed: A365.1, A365.2, IC31.13
unnamed: A364.1, A364.2, IC31.12
unnamed: A363.1, A363.2, IC31.11
unnamed: A353.1, A353.2, IC31.1
unnamed: A360.1, A360.2, IC31.8
unnamed: A354.1, A354.2, IC31.2
unnamed: A359.1, A359.2, IC31.7
unnamed: A355.1, A355.2, IC31.3
unnamed: A356.1, A356.2, IC31.4
unnamed: A357.1, A357.2, IC31.5
unnamed: A358.1, A358.2, IC31.6
unnamed: A384.1, A384.2, IC32.16
unnamed: A377.1, A377.2, IC32.9
unnamed: A383.1, A383.2, IC32.15
unnamed: A378.1, A378.2, IC32.10
unnamed: A382.1, A382.2, IC32.14
unnamed: A381.1, A381.2, IC32.13
unnamed: A380.1, A380.2, IC32.12
unnamed: A379.1, A379.2, IC32.11
unnamed: A369.1, A369.2, IC32.1
unnamed: A376.1, A376.2, IC32.8
unnamed: A370.1, A370.2, IC32.2
unnamed: A375.1, A375.2, IC32.7
unnamed: A371.1, A371.2, IC32.3
unnamed: A372.1, A372.2, IC32.4
unnamed: A373.1, A373.2, IC32.5
unnamed: A374.1, A374.2, IC32.6
unnamed: A400.1, A400.2, IC33.16
unnamed: A393.1, A393.2, IC33.9
unnamed: A399.1, A399.2, IC33.15
unnamed: A394.1, A394.2, IC33.10
unnamed: A398.1, A398.2, IC33.14
unnamed: A397.1, A397.2, IC33.13
unnamed: A396.1, A396.2, IC33.12
unnamed: A395.1, A395.2, IC33.11
unnamed: A385.1, A385.2, IC33.1
unnamed: A392.1, A392.2, IC33.8
unnamed: A386.1, A386.2, IC33.2
unnamed: A391.1, A391.2, IC33.7
unnamed: A387.1, A387.2, IC33.3
unnamed: A388.1, A388.2, IC33.4
unnamed: A389.1, A389.2, IC33.5
unnamed: A390.1, A390.2, IC33.6
unnamed: A416.1, A416.2, IC34.16
unnamed: A409.1, A409.2, IC34.9
unnamed: A415.1, A415.2, IC34.15
unnamed: A410.1, A410.2, IC34.10
unnamed: A414.1, A414.2, IC34.14
unnamed: A413.1, A413.2, IC34.13
unnamed: A412.1, A412.2, IC34.12
unnamed: A411.1, A411.2, IC34.11
unnamed: A401.1, A401.2, IC34.1
unnamed: A408.1, A408.2, IC34.8
unnamed: A402.1, A402.2, IC34.2
unnamed: A407.1, A407.2, IC34.7
unnamed: A403.1, A403.2, IC34.3
unnamed: A404.1, A404.2, IC34.4
unnamed: A405.1, A405.2, IC34.5
unnamed: A406.1, A406.2, IC34.6
unnamed: A432.1, A432.2, IC35.16
unnamed: A425.1, A425.2, IC35.9
unnamed: A431.1, A431.2, IC35.15
unnamed: A426.1, A426.2, IC35.10
unnamed: A430.1, A430.2, IC35.14
unnamed: A429.1, A429.2, IC35.13
unnamed: A428.1, A428.2, IC35.12
unnamed: A427.1, A427.2, IC35.11
unnamed: A417.1, A417.2, IC35.1
unnamed: A424.1, A424.2, IC35.8
unnamed: A418.1, A418.2, IC35.2
unnamed: A423.1, A423.2, IC35.7
unnamed: A419.1, A419.2, IC35.3
unnamed: A420.1, A420.2, IC35.4
unnamed: A421.1, A421.2, IC35.5
unnamed: A422.1, A422.2, IC35.6
unnamed: A448.1, A448.2, IC36.16
unnamed: A441.1, A441.2, IC36.9
unnamed: A447.1, A447.2, IC36.15
unnamed: A442.1, A442.2, IC36.10
unnamed: A446.1, A446.2, IC36.14
unnamed: A445.1, A445.2, IC36.13
unnamed: A444.1, A444.2, IC36.12
unnamed: A443.1, A443.2, IC36.11
unnamed: A433.1, A433.2, IC36.1
unnamed: A440.1, A440.2, IC36.8
unnamed: A434.1, A434.2, IC36.2
unnamed: A439.1, A439.2, IC36.7
unnamed: A435.1, A435.2, IC36.3
unnamed: A436.1, A436.2, IC36.4
unnamed: A437.1, A437.2, IC36.5
unnamed: A438.1, A438.2, IC36.6
VCC: VCC1.1, VCC1.2, VCC2.1, VCC2.2, VCC3.1, VCC3.2, VCC4.1, VCC4.2, VCC5.1, VCC5.2, VCC6.1, VCC6.2, VCC7.1, VCC7.2, VCC8.1, VCC8.2, VCC9.1, VCC9.2, VCC10.1, VCC10.2, VCC11.1, VCC11.2, VCC12.1, VCC12.2, VCC13.1, VCC13.2, VCC14.1, VCC14.2, VCC15.1, VCC15.2, VCC16.1, VCC16.2, VCC17.1, VCC17.2, VCC18.1, VCC18.2, VCC19.1, VCC19.2, VCC20.1, VCC20.2, VCC21.1, VCC21.2, VCC22.1, VCC22.2, VCC23.1, VCC23.2, VCC24.1, VCC24.2, VCC25.1, VCC25.2, VCC26.1, VCC26.2, VCC27.1, VCC27.2, VCC28.1, VCC28.2, VCC29.1, VCC29.2, VCC30.1, VCC30.2, VCC31.1, VCC31.2, VCC32.1, VCC32.2, VCC33.1, VCC33.2, VCC34.1, VCC34.2, VCC35.1, VCC35.2, VCC36.1, VCC36.2, VCC37.1, VCC37.2, VCC38.1, VCC38.2, VCC39.1, VCC39.2, VCC40.1, VCC40.2, VCC41.1, VCC41.2, VCC42.1, VCC42.2, VCC43.1, VCC43.2, VCC44.1, VCC44.2; also elsewhere on the board

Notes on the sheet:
16 Pin Socket Areas
Douglas Electronics
